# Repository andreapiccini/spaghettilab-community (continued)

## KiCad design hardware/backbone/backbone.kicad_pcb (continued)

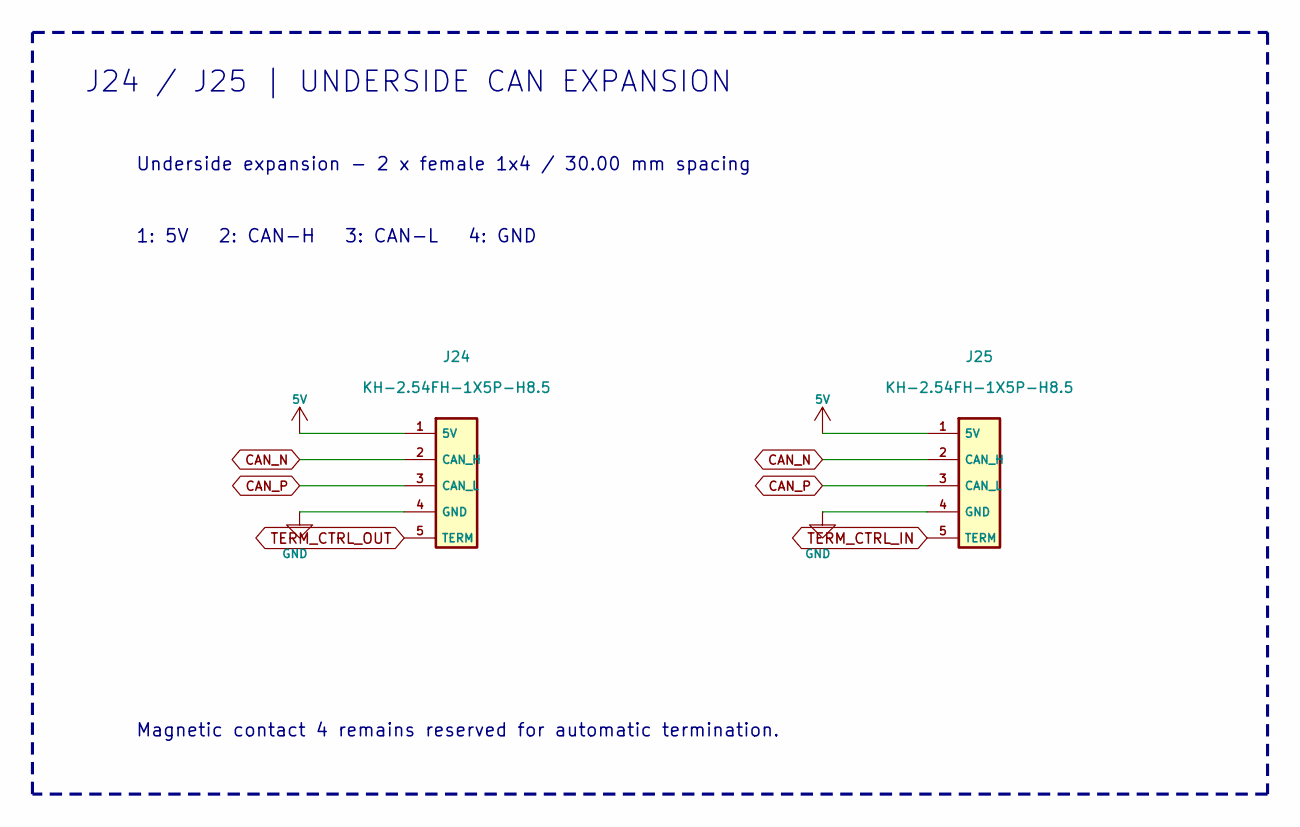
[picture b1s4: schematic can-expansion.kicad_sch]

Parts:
J24, J25: KH-2.54FH-1X5P-H8.5; Female_1x05_P2.54_H8.5; LCSC C2932671

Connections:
5V: J24.1 (5V), J25.1 (5V); also elsewhere on the board
CAN_N: J24.2 (CAN_H), J25.2 (CAN_H); also elsewhere on the board
CAN_P: J24.3 (CAN_L), J25.3 (CAN_L); also elsewhere on the board
GND: J24.4 (GND), J25.4 (GND); also elsewhere on the board
TERM_CTRL_IN: J25.5 (TERM); also elsewhere on the board
TERM_CTRL_OUT: J24.5 (TERM); also elsewhere on the board

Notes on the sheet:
1: 5V 2: CAN-H 3: CAN-L 4: GND
Underside expansion - 2 x female 1x4 / 30.00 mm spacing
Magnetic contact 4 remains reserved for automatic termination.
J24 / J25 | UNDERSIDE CAN EXPANSION

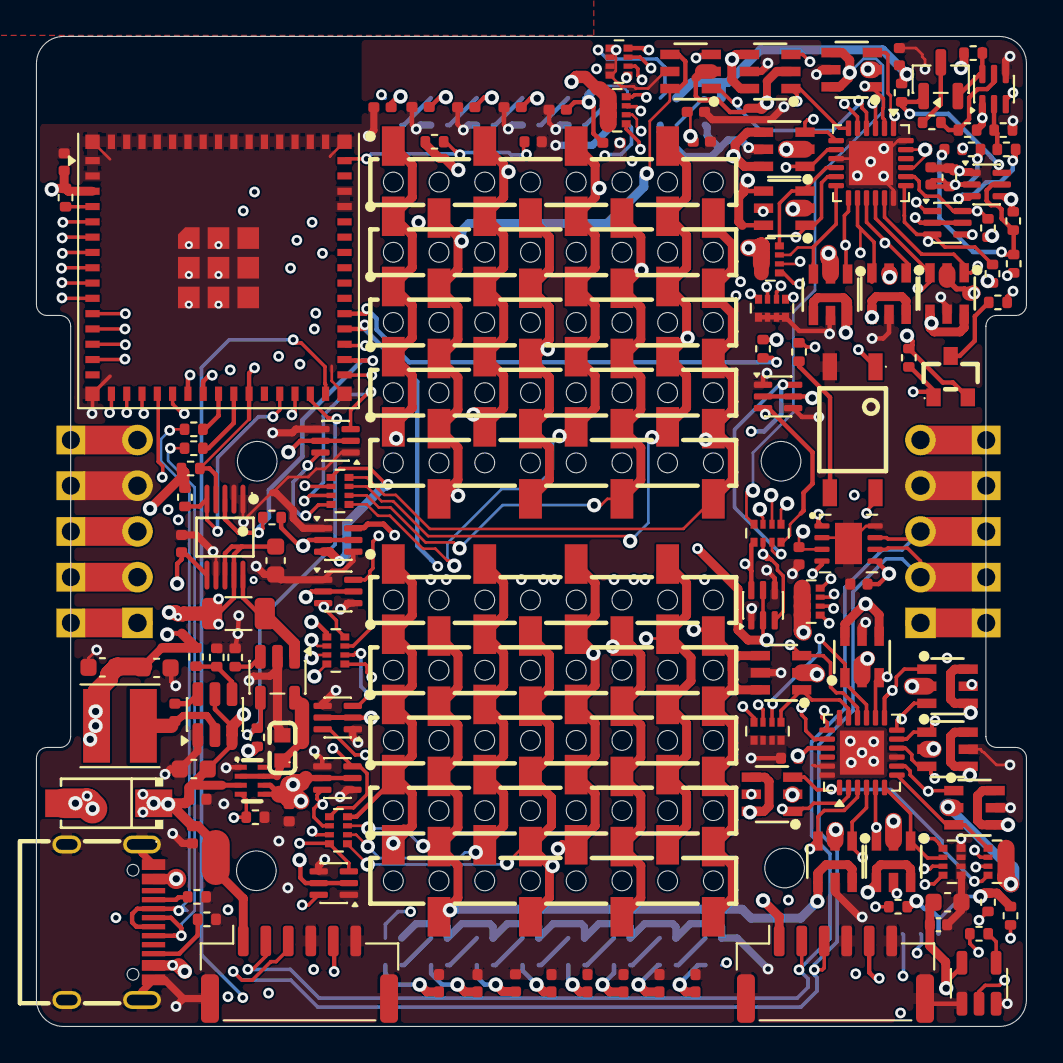
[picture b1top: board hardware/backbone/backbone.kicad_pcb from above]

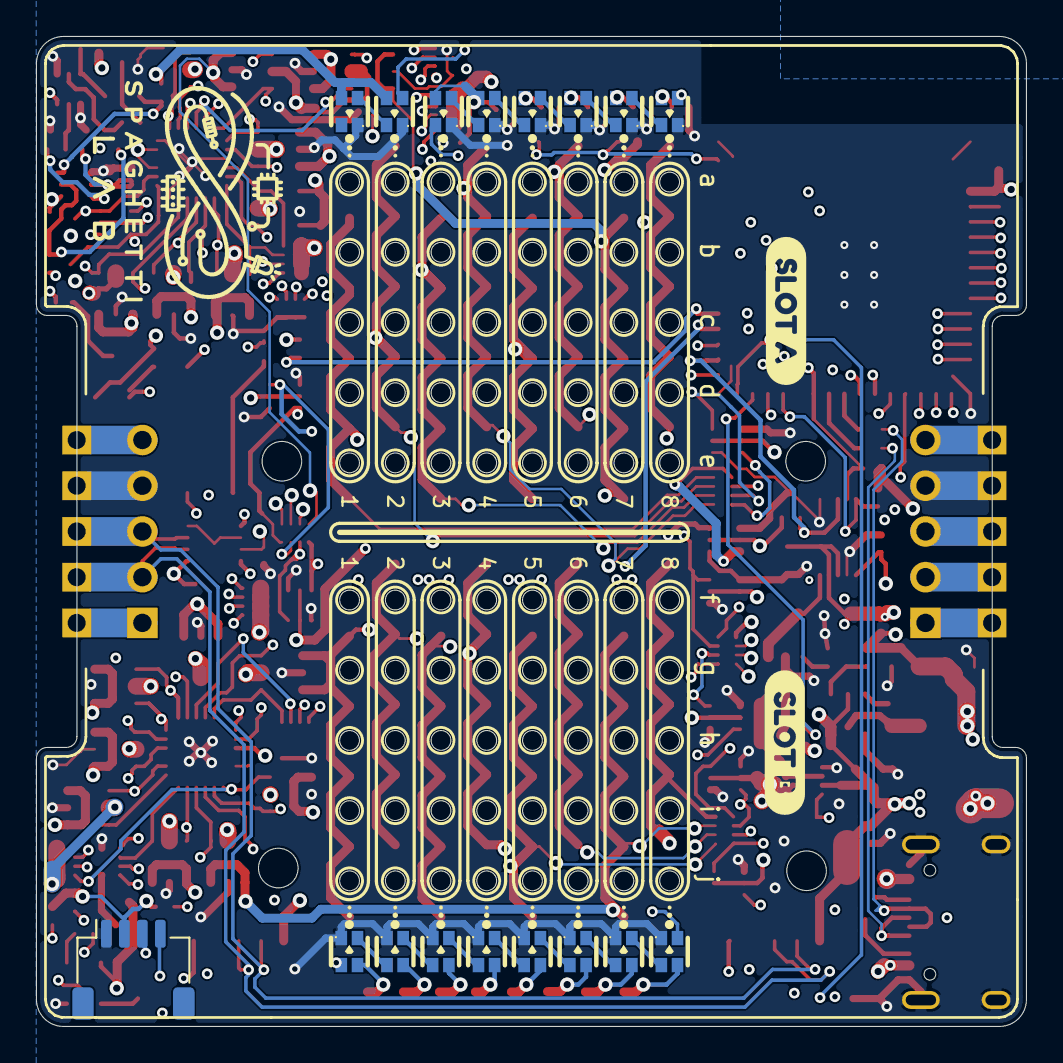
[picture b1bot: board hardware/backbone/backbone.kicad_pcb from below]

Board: 6 copper layers, 55.0 x 55.0 mm, 164 parts (19 on the bottom side), 129 nets.

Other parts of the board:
kobee-studio-6B0996DB: Kobee Studio; kobee-studio-6B0996DB
kobee-studio-6B0996F7: Kobee Studio; kobee-studio-6B0996F7

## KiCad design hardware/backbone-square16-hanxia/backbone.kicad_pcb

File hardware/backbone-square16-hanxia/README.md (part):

# Revisione attuale PANEL16 / FFC60 — 10 novembre 2026

Schema e PCB aggiornati:78×78mm,16touch su U91,STOP/LOCK,61LED pannello,FFC60 J32 e asola. Leggere [PANEL16-FFC60.md](PANEL16-FFC60.md) e panel16-ffc60-verification.json. Firmware non portato; routing,DRC e ottica ancora da completare. Le sezioni precedenti sul pannello32touch/U90 non descrivono più il circuito attivo. Mappa dual-MCU aggiornata a 9/9 ADC: vedere ADC99-WIRING.md.

---

# Revisione dual MCU — 10 novembre 2026

Riferimento: backbone-square16-hanxia salvato su disco. Questa revisione conserva le posizioni di tutti i componenti preesistenti, tutte le 16 righe, piste e zone; aggiunge R923 10k 0603. Schema e PCB sono sincronizzati. Nessun MEZZ_PRESENT_N esiste in questa versione: il pad31 è ora la riga R05.

Moduli previsti: ESP32-S3-WROOM-1-N8R2 e ESP32-S31-WROOM-1-N16R16V, antenna PCB, socket perimetrale a40contatti. Altre varianti richiedono revisione: in particolare S3 con PSRAM octal usa i pad28–30 e non garantisce le16righe. Nomi rete GPIOxx e pin del simbolo sono alias S3, non numeri S31. Usare dual-mcu-pinout.csv e dual-mcu-profiles.json.

ADC sulle righe: S3 A1-A5 e B1-B4 (9 ADC1); S31 A1/A6-A8 e B1/B5-B8 (6 ADC1 + 3 ADC2). Comuni A1 e B1. Banco A: 5/4; banco B: 4/5 (S3/S31). DAC S31 su A3/A4. I2C_INT_SDA sul pad25 (S3 GPIO48 / S31 GPIO40); il pad4 diventa A5. Vedere dual-mcu-rows.csv. I GPIO delle derivazioni J26/J27 e FFC60 J32 seguono le nuove righe.

Correzioni: R201 diventa10k tra3V3 e pad21/STRAP_SPI_VOLTAGE; nessun pull esterno sul pad26, che segue i diversi default interni dei due moduli. U91 SDA passa al pad8, VBUS sense al pad24. ROW_ARM_N usa pad22 con nuovo pull-upR923 e pilota U60. BOOT pad27 non abilita più le righe. Non usare GPIO hold su ROW_ARM_N; rispettare almeno3ms dopo il rilascio EN prima di modificare gli strap.

J25.7/.8/.12, J26.22/.24 e J27.22 sono NC riservati: rimosso l'accesso esterno a strap flash e segnali riservati. Restano due GPIO ausiliari sui pad36/37; TX UART0 può emettere log al boot. Connettori aggiornati in dual-mcu-connectors.csv. Non collegare mai direttamente GPIO eROW sulla mezzanina.

USB: programmazione e seriale/JTAG comuni sui pad13/14. USB OTG/host applicativo disponibile sul socket solo conS3; S31 High-Speed richiede pad54/55 inferiori non contattati. CAN resta classico con SN65HVD230; non attivare CAN-FD bitrate switching. I2C interno ed esterno restano separati; U91 resta su softwareI2C dedicato.

Alimentazione: SY8089AAAC nominale2A, 3,31V circa (150k/33,2k), bypass22uF e EN10k/1uF presenti. Budget condiviso: riservare almeno600mA al moduloS31, oltre a transceiver, logica e carichi; non considerare1A delle righe sommabile senza limiti ai carichi dei connettori. Termica, transitori e contatti FlexyPin da misurare.

Firmware: i profili JSON sono il contratto della nuova scheda, non un firmware funzionante. Il firmware presente nel repository usa una precedente mappa di scheda; non è stato portato su Hanxia/S31. Implementare inizializzazione controls16.json, selezione capacità per riga, USB host disabilitato su S31, ADC calibrato secondo SDK per target e reset fail-safe. Nessuna prova su hardware fisico eseguita.

NON PRONTA PER PRODUZIONE: zero errori ERC, 66avvisi; 1207pad verificati senza differenze di rete schema/PCB. Restano499connessioni da sbrogliare e problemi DRC preesistenti (incluse sovrapposizioni, fori/maschera/clearance, keepout). R923 non introduce rilievi DRC. Le variazioni nel numero di coppie di fori segnalate non derivano da spostamenti: la geometria originale è stata verificata identica. Completare sbroglio, DRC, controllo meccanico del socket e prove di alimentazione/reset/USB/ADC prima di ordinare PCB assemblati.

Le sezioni storiche seguenti non prevalgono su questa revisione; studi e immagini precedenti non rappresentano la mappa attuale. Vedere dual-mcu-review.html e dual-mcu-verification.json.

---

## Current main project — touch controls applied

Open `backbone.kicad_pro` in this folder. SW1/SW2 are removed from the native schematic and PCB; U91 and nine global touch electrodes are present. See `CURRENT-REVIEW-STATE.md` and `touch-applied-verification.json` for the current status. Routing and firmware remain unfinished. Earlier sections below describe historical design stages.

## Revisione: quattro colonne per banco

Aggiunti J30 eJ31, Hanxia HX PM2.54-1x8P TP-YQ C42380985: quattro connettori per banco, otto righe per banco e64contatti accessibili complessivi. I quattro contatti della stessa riga condividono la reteROW_Lxx oROW_Rxx; restano16righe programmabili e gli stessiGPIO/driver. Passo tra righe2,54mm; passo tra colonne dello stesso banco4mm, mantenuto per l’ingombro Hanxia. Separazione tra le due colonne interne7,62mm per gli integratiDIP.

La scheda passa da70x66 a78x66mm, con magnetici a metà altezza eUSB laterale. Indicatori laterali e serigrafia breadboard spostati e allungati. Due soli connettori aggiunti alla distinta; costo totale da aggiornare. Bottom access del connettore resta da qualificare sul campione fisico.

Schema ePCB aggiornati e confrontati:64pad dei connettori sulle16reti corrette, nessun cambiamento alle reti preesistenti, ERC0errori. Restano avvisiDRC e routing rame incompleto; la scheda non è ancora pronta per produzione. L’anteprima accesa è una simulazione ottica, il firmware dei comandi resta da implementare. Le sezioni seguenti descrivono revisioni precedenti.

## Revisione: logo, configurazione e selezione globale

Logo con16LED blu su griglia4x4, mantenendo il disegno vettoriale. Aggiunti CONFIG ON verde/OFF rosso, DELETE rosso accanto aLOAD/SAVE eALL verde accanto alle selezioniA/B. BUS identifica i contatti magnetici; EXP e i nomiGND/DET/CANL/CANH/5V/3V3/SDA/SCL distinguono gli attacchi laterali dalla breadboard. ESP EXP e il marcatore1 identificano il connettore sud. La serigrafia informa, ma non impedisce meccanicamente inserimenti errati.

112LED complessivi,109canali del driver usati,35liberi: nessun driver aggiunto. Il logo passa da9a16LED; gli altri4nuoviLED sonoON/OFF/DELETE/ALL. Ingombro invariato70x66mm. Prezzo totale da ricalcolare.

Comandi proposti, NON implementati nel firmware: tenere RIGHE1s selezionaALL (maschera0xffff), cioè tutte le16righe, senza collegarle elettricamente tra loro. Nei menu la pressione lungaRIGHE mantiene la funzione annulla. Tenere entrambi i tasti1s commutaON/OFF, con priorità sulla lettura dei singoli clic. OFF disattiva i percorsi delle righe mettendole inHi-Z e conserva la configurazione in memoria; ESP32, USB e alimentazioni fisse dei connettori di espansione rimangono alimentati. ON indica l’applicazione software riuscita, non una misura elettrica. In anteprimaOFF, lampeggiare o attenuare le modalità per distinguerle dall’uscita applicata.

Tre clicRIGHE aprono il menu slot1..4; RIGHE sceglie lo slot eMODO scorreLOAD/SAVE/DELETE. DoppioMODO confermaLOAD/SAVE; perDELETE richiedereMODO1.5s. DELETE cancella solo lo slot persistente, senza alterare uscite e configurazione attiva. LOAD confermato deve prima disarmare le uscite, caricare il profilo come bozzaOFF e richiedere una successiva confermaON. Navigare gli slot non modifica le uscite. SAVE conserva modalità, profiloMCU, pull e parametri in formato versionato. ADC non ammesso suALL perché il bancoB non dispone diADC interno; le risorsePWM vanno validate. Nessun aggiornamento firmware incluso.

Anteprima accesa ideale: ALL selezionato, CONFIG ON, tutte le righeMCU IN conPULL UP, SAVE e slot2 selezionati. Le luci simulano le aperture reali della maschera, non la resa fotometrica. QualificareFR4, orientamento ottico e diffusione con un prototipo. Routing ancora incompleto eDRC generale non risolto: non pronto per produzione. Verifiche attuali in ui-integration-verification.json; seguono note storiche delle revisioni precedenti.

## Revisione attuale: PIN MODE e pull interni

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
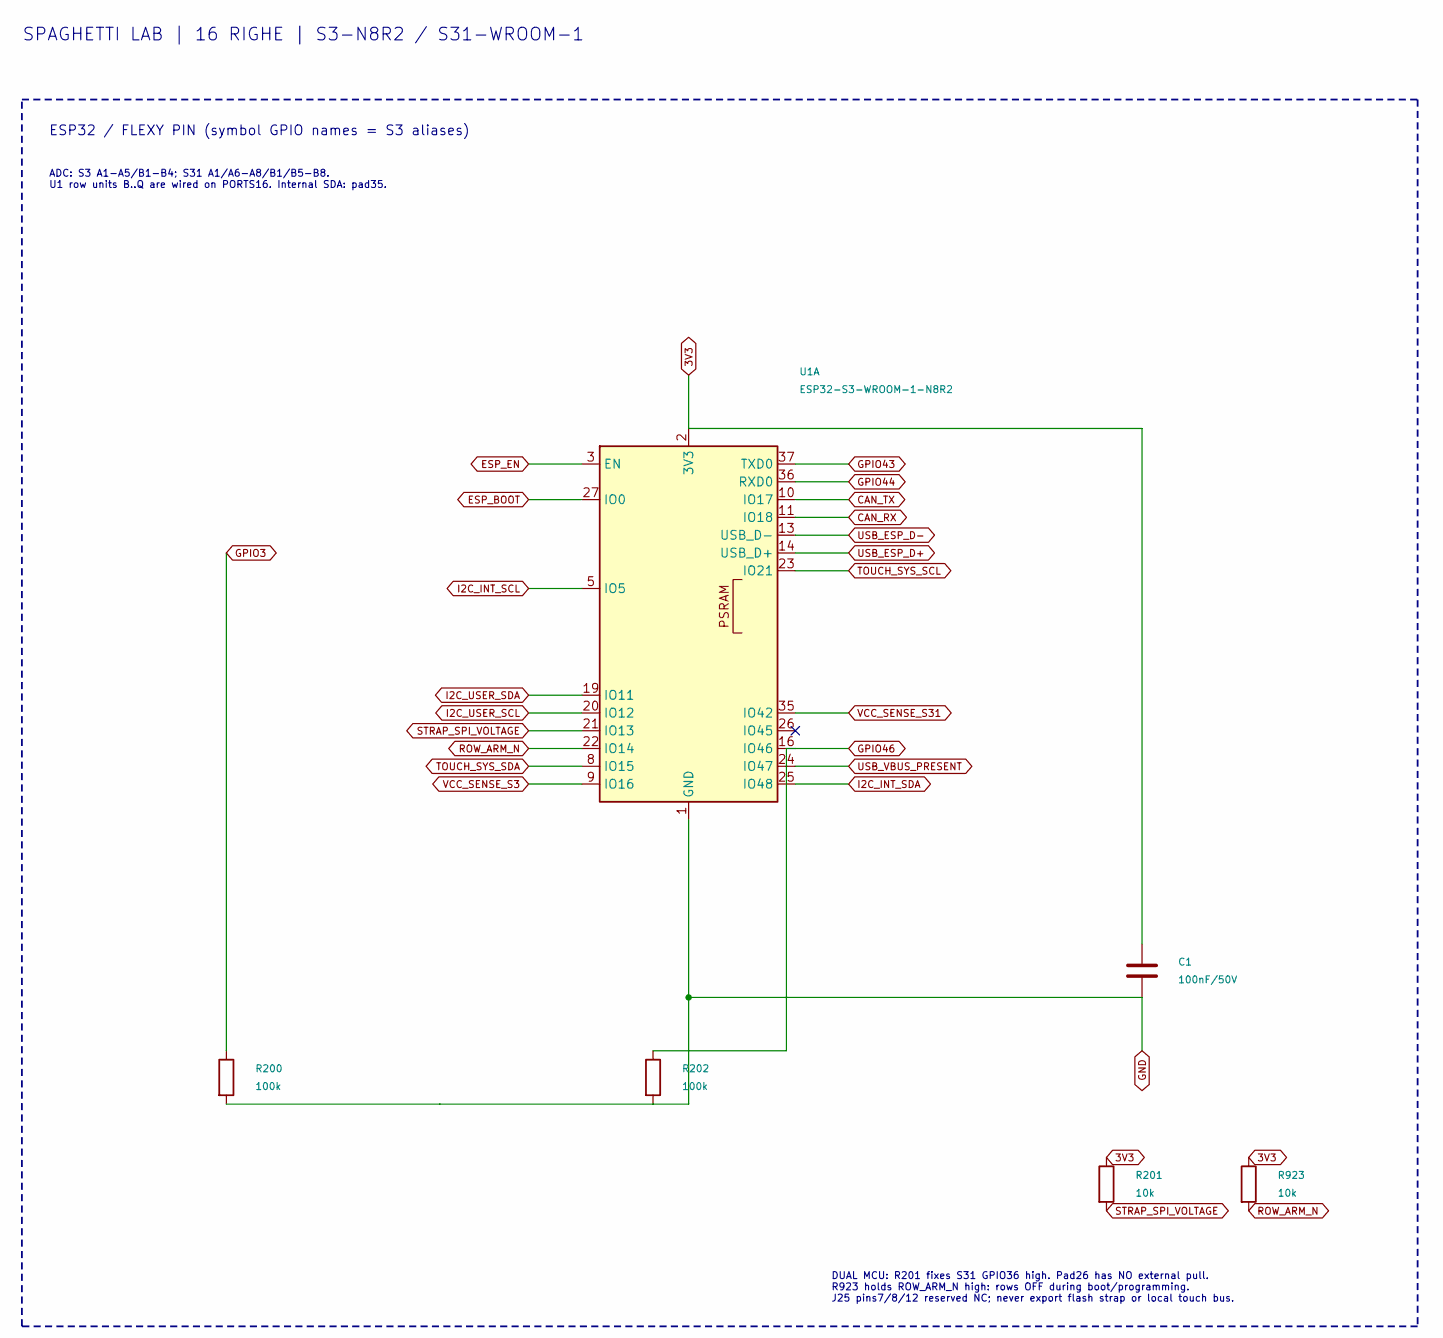
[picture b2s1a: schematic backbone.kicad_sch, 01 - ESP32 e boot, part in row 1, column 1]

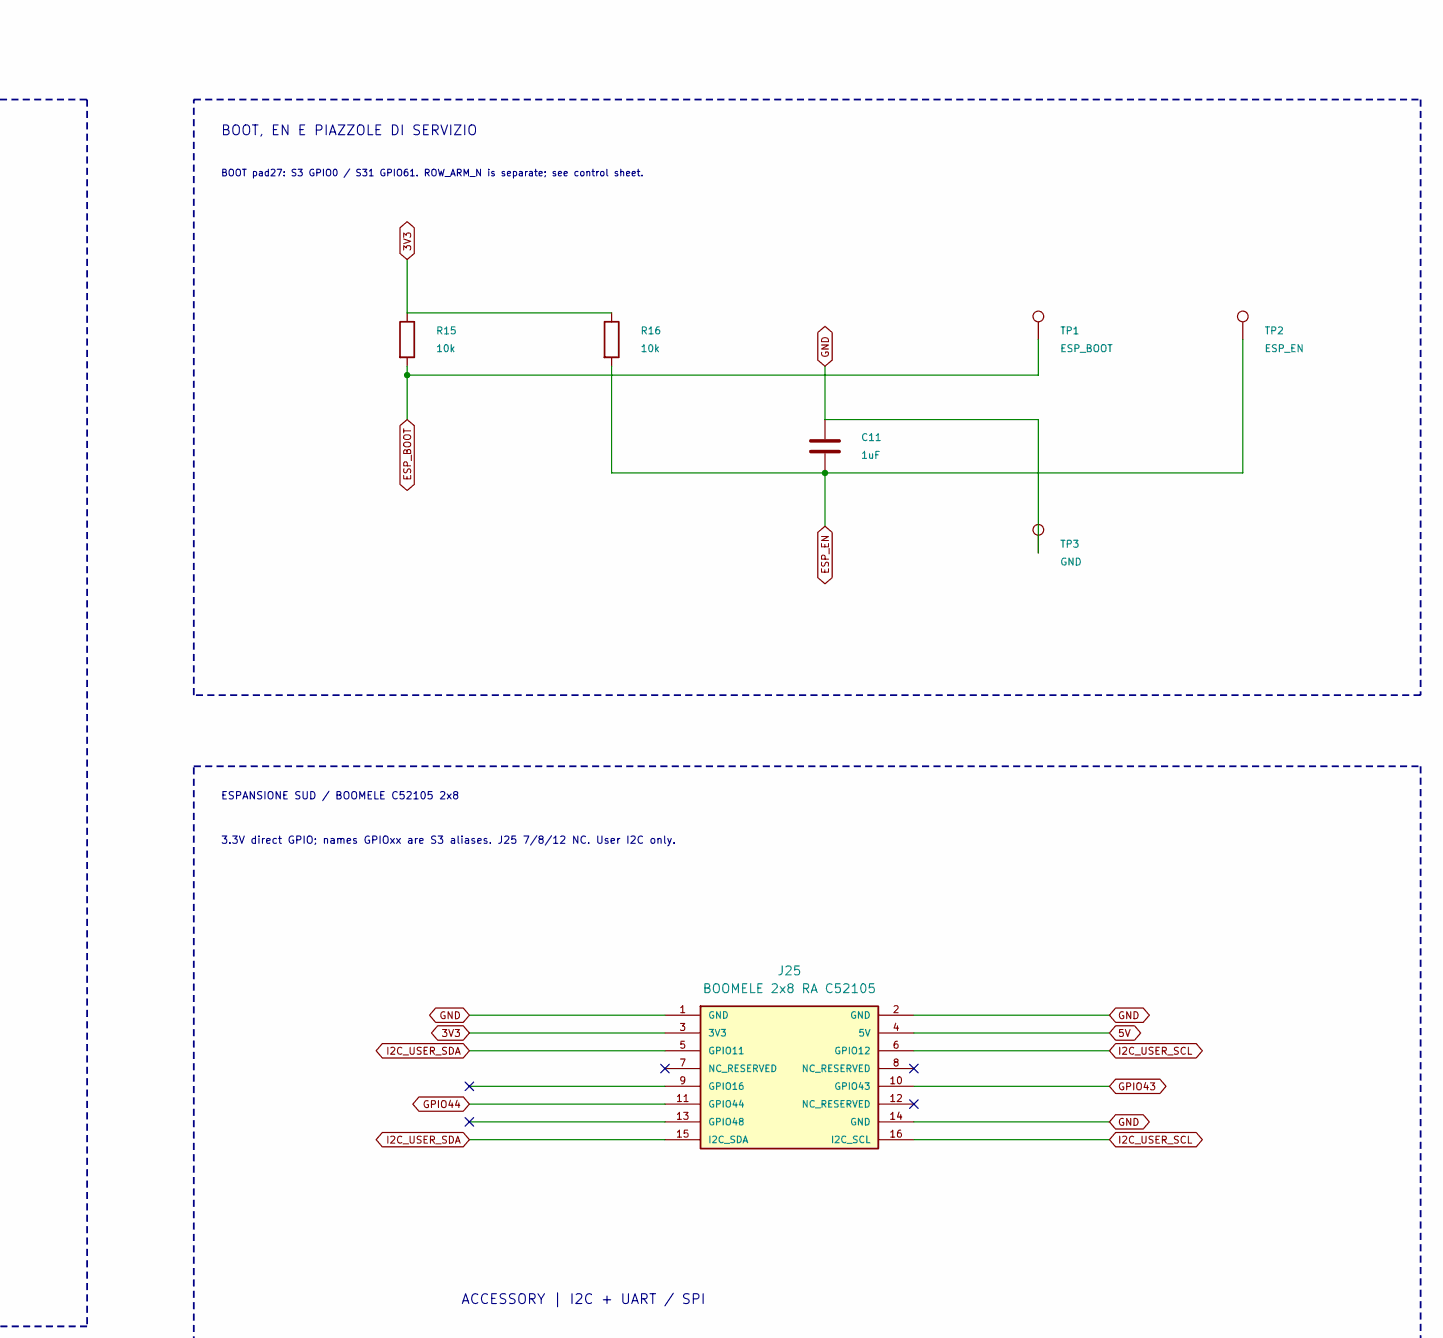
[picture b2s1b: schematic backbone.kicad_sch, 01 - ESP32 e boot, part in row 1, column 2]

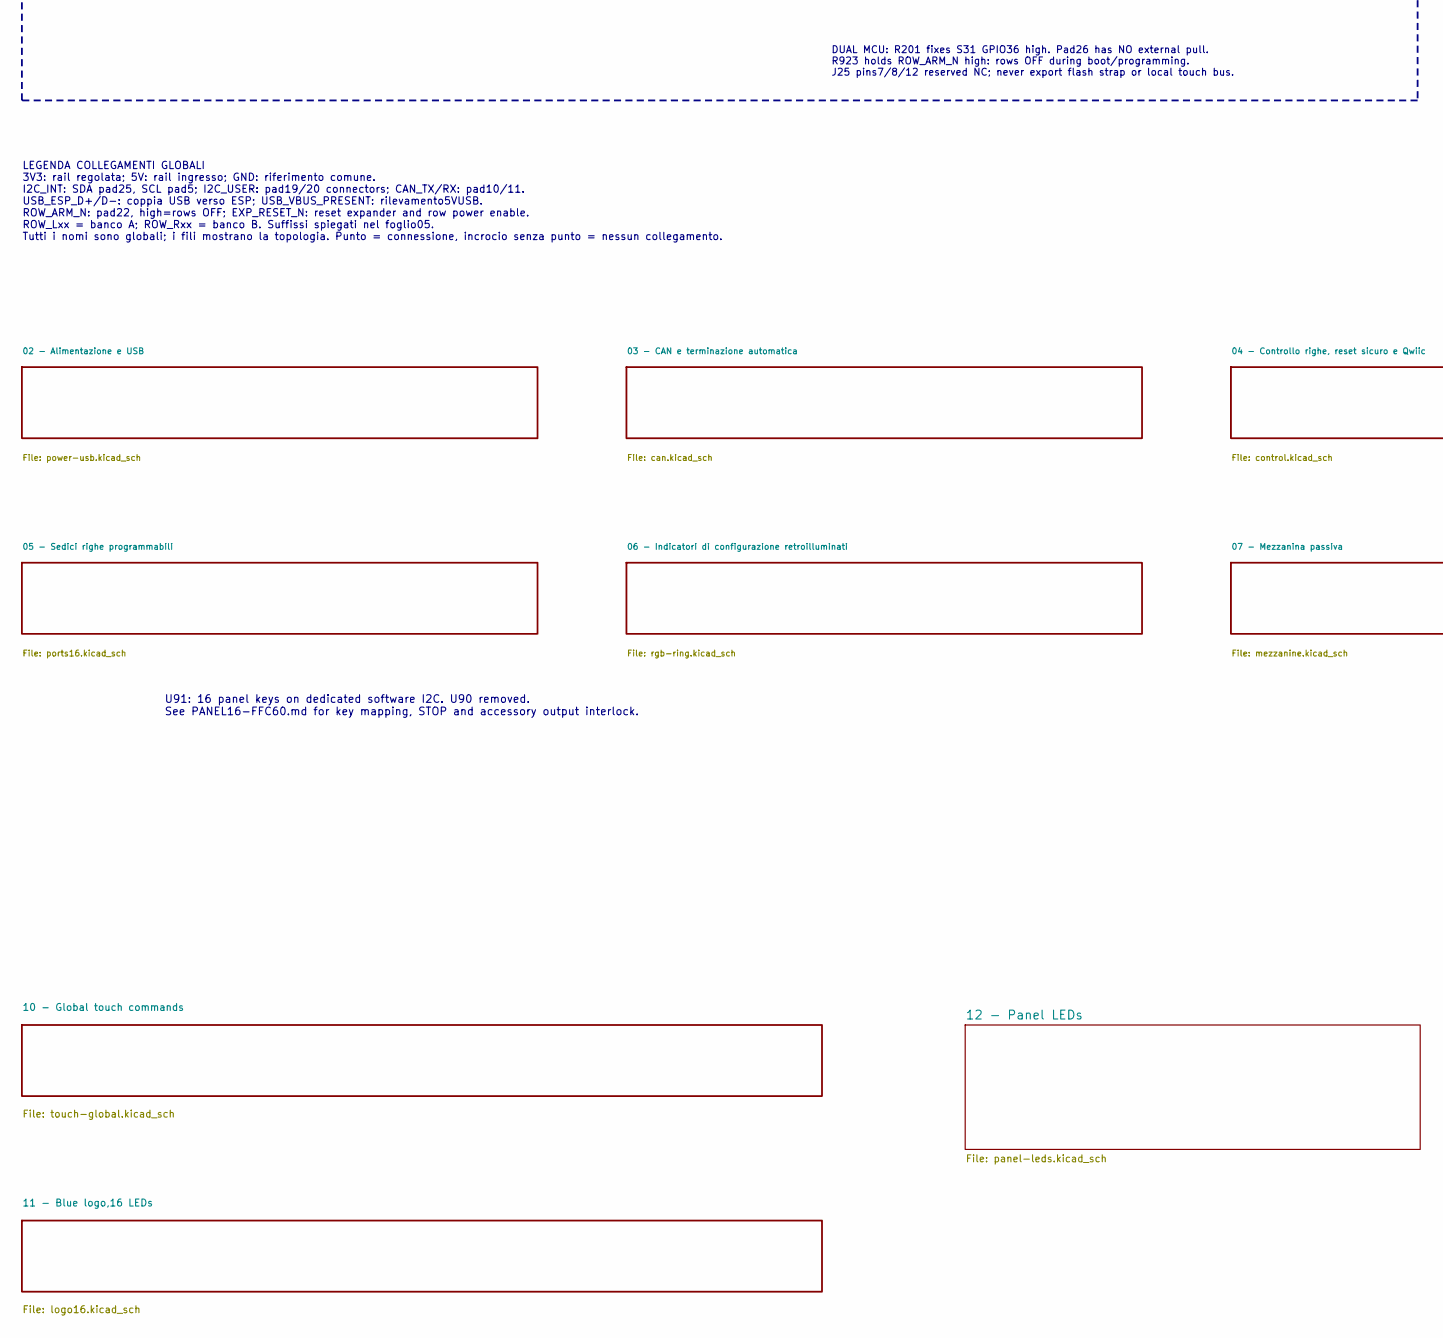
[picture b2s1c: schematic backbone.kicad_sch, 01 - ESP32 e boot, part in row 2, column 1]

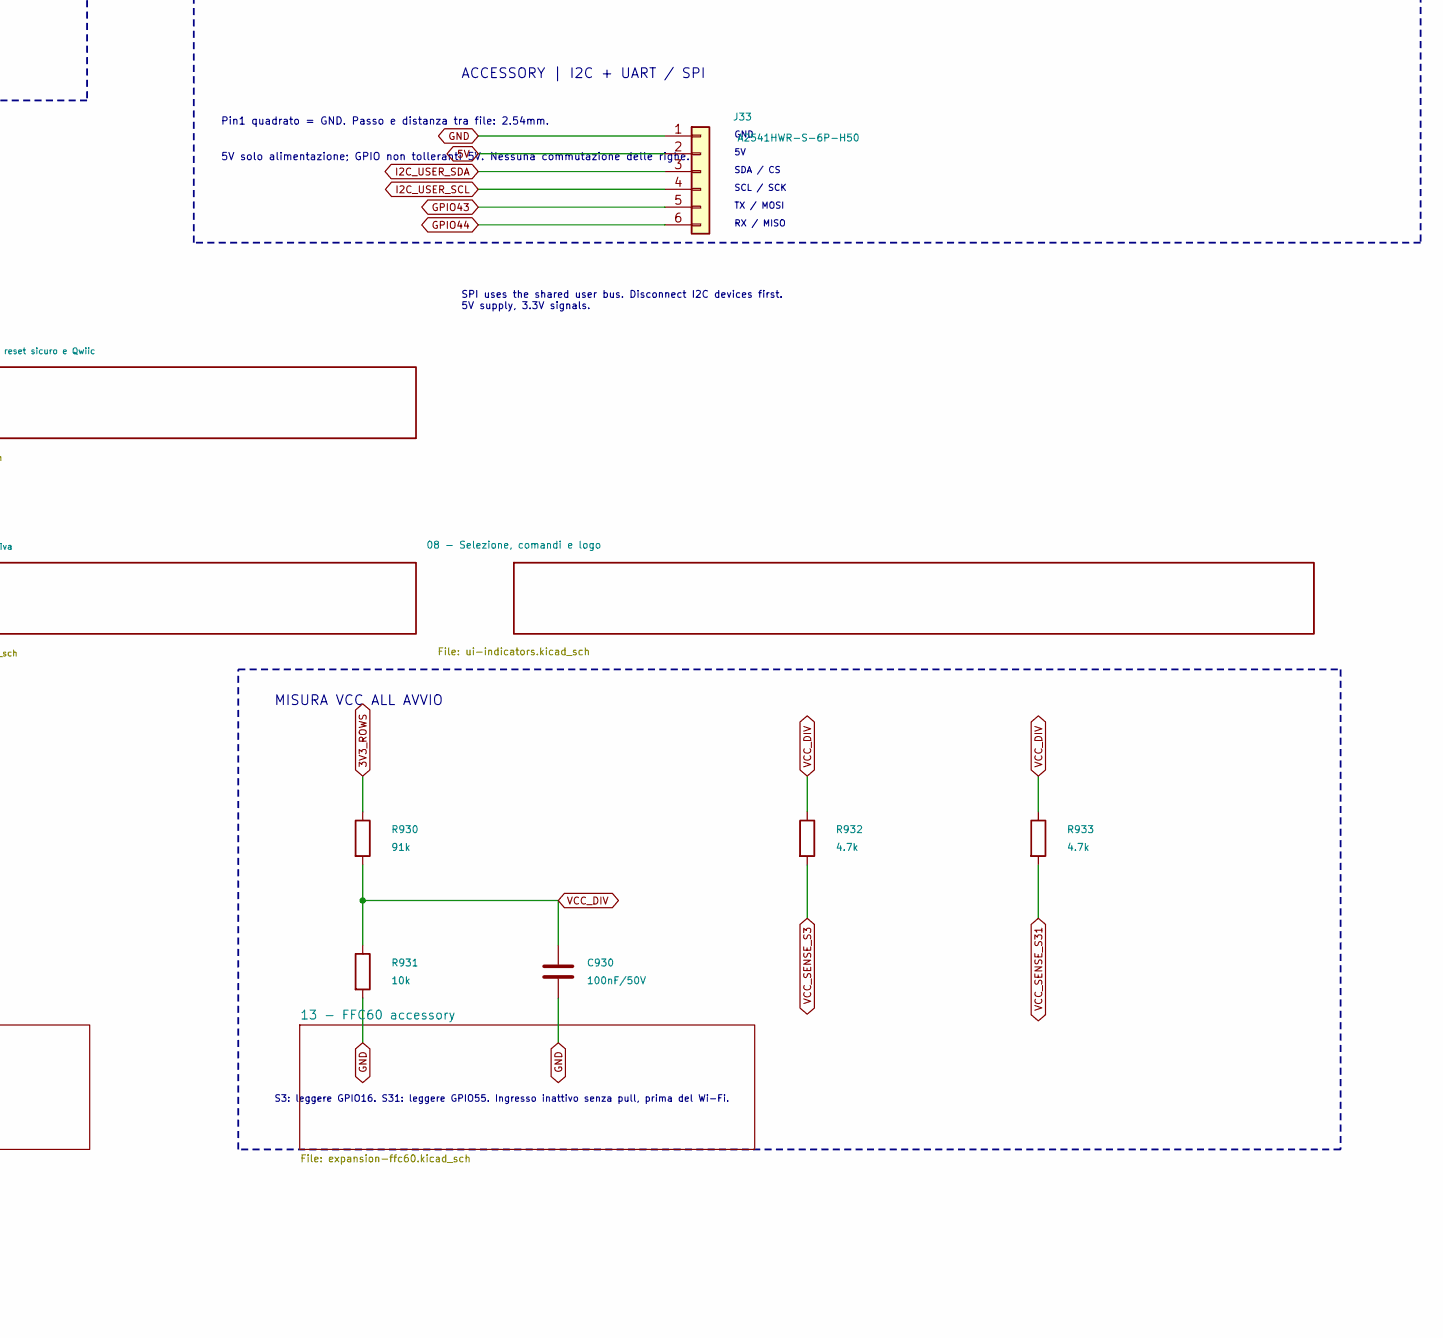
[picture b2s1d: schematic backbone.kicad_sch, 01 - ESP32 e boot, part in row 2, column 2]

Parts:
C1: 100nF/50V; C0603; MPN CL10B104KB8NNNC; LCSC Part Name C1591
C11: 1uF; C0603; LCSC Part Name C128624
C930: 100nF/50V; C0603
J25: BOOMELE 2x8 RA C52105; BOOMELE_C52105_2x08_RightAngle
J33: A2541HWR-S-6P-H50; CJT_A2541HWR-S-6P-H50
R15, R16: 10k; R0603; MPN 0603WAF1002T5E; LCSC Part C25804
R200, R202: 100k; R_0603_1608Metric
R201: 10k; R_0603_1608Metric
R923: 10k; R_0603_1608Metric; MPN 0603WAF1002T5E; LCSC Part C25804
R930: 91k; R0603
R931: 10k; R0603
R932, R933: 4.7k; R0603
TP1: ESP_BOOT; TestPoint_Pad_D1.5mm
TP2: ESP_EN; TestPoint_Pad_D1.5mm
TP3: GND; TestPoint_Pad_D1.5mm
U1: ESP32-S3-WROOM-1-N8R2; ESP32-S3-WROOM-1_FlexyPin_N8R2_TwoSideCourtyard; MPN ESP32-S3-WROOM-1-N8R2

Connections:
3V3: C1.1, J25.3 (3V3), R15.1, R16.1, R201.1, R923.1, U1.2 (3V3); also elsewhere on the board
3V3_ROWS: R930.1; also elsewhere on the board
5V: J25.4 (5V), J33.2; also elsewhere on the board
CAN_RX: U1.11 (IO18); also elsewhere on the board
CAN_TX: U1.10 (IO17); also elsewhere on the board
ESP_BOOT: R15.2, TP1.1, U1.27 (IO0)
ESP_EN: C11.2, R16.2, TP2.1, U1.3 (EN); also elsewhere on the board
GND: C1.2, C11.1, C930.2, J25.1 (GND), J25.2 (GND), J25.14 (GND), J33.1, R200.2, R202.2, R931.2, TP3.1, U1.1 (GND), U1.40 (GND); also elsewhere on the board
GPIO3: R200.1; also elsewhere on the board
GPIO43: J25.10 (GPIO43), J33.5, U1.37 (TXD0); also elsewhere on the board
GPIO44: J25.11 (GPIO44), J33.6, U1.36 (RXD0); also elsewhere on the board
GPIO46: R202.1, U1.16 (IO46)
I2C_INT_SCL: U1.5 (IO5); also elsewhere on the board
I2C_INT_SDA: U1.25 (IO48); also elsewhere on the board
I2C_USER_SCL: J25.6 (GPIO12), J25.16 (I2C_SCL), J33.4, U1.20 (IO12); also elsewhere on the board
I2C_USER_SDA: J25.5 (GPIO11), J25.15 (I2C_SDA), J33.3, U1.19 (IO11); also elsewhere on the board
ROW_ARM_N: R923.2, U1.22 (IO14); also elsewhere on the board
STRAP_SPI_VOLTAGE: R201.2, U1.21 (IO13)
TOUCH_SYS_SCL: U1.23 (IO21); also elsewhere on the board
TOUCH_SYS_SDA: U1.8 (IO15); also elsewhere on the board
USB_ESP_D+: U1.14 (USB_D+); also elsewhere on the board
USB_ESP_D-: U1.13 (USB_D-); also elsewhere on the board
USB_VBUS_PRESENT: U1.24 (IO47); also elsewhere on the board
VCC_DIV: C930.1, R930.2, R931.1, R932.1, R933.1
VCC_SENSE_S3: R932.2, U1.9 (IO16)
VCC_SENSE_S31: R933.2, U1.35 (IO42)

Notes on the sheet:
SPAGHETTI LAB | 16 RIGHE | S3-N8R2 / S31-WROOM-1
ESP32 / FLEXY PIN (symbol GPIO names = S3 aliases)
ADC: S3 A1-A5/B1-B4; S31 A1/A6-A8/B1/B5-B8. U1 row units B..Q are wired on PORTS16. Internal SDA: pad35.
BOOT, EN E PIAZZOLE DI SERVIZIO
BOOT pad27: S3 GPIO0 / S31 GPIO61. ROW_ARM_N is separate; see control sheet.
LEGENDA COLLEGAMENTI GLOBALI 3V3: rail regolata; 5V: rail ingresso; GND: riferimento comune. I2C_INT: SDA pad25, SCL pad5; I2C_USER: pad19/20 connectors; CAN_TX/RX: pad10/11. USB_ESP_D+/D-: coppia USB verso ESP; USB_VBUS_PRESENT: rilevamento5VUSB. ROW_ARM_N: pad22, high=rows OFF; EXP_RESET_N: reset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
ESPANSIONE SUD / BOOMELE C52105 2x8
3.3V direct GPIO; names GPIOxx are S3 aliases. J25 7/8/12 NC. User I2C only.
Pin1 quadrato = GND. Passo e distanza tra file: 2.54mm.
5V solo alimentazione; GPIO non tolleranti 5V. Nessuna commutazione delle righe.
U91: 16 panel keys on dedicated software I2C. U90 removed. See PANEL16-FFC60.md for key mapping, STOP and accessory output interlock.
DUAL MCU: R201 fixes S31 GPIO36 high. Pad26 has NO external pull. R923 holds ROW_ARM_N high: rows OFF during boot/programming. J25 pins7/8/12 reserved NC; never export flash strap or local touch bus.
MISURA VCC ALL AVVIO
S3: leggere GPIO16. S31: leggere GPIO55. Ingresso inattivo senza pull, prima del Wi-Fi.
ACCESSORY | I2C + UART / SPI
SPI uses the shared user bus. Disconnect I2C devices first. 5V supply, 3.3V signals.
GND
SDA / CS
SCL / SCK
TX / MOSI
RX / MISO
